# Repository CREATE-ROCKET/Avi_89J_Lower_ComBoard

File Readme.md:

> [!WARNING]
> Kicad v8を用いて作成したため、これ以下のバージョンのkicadだと動きません

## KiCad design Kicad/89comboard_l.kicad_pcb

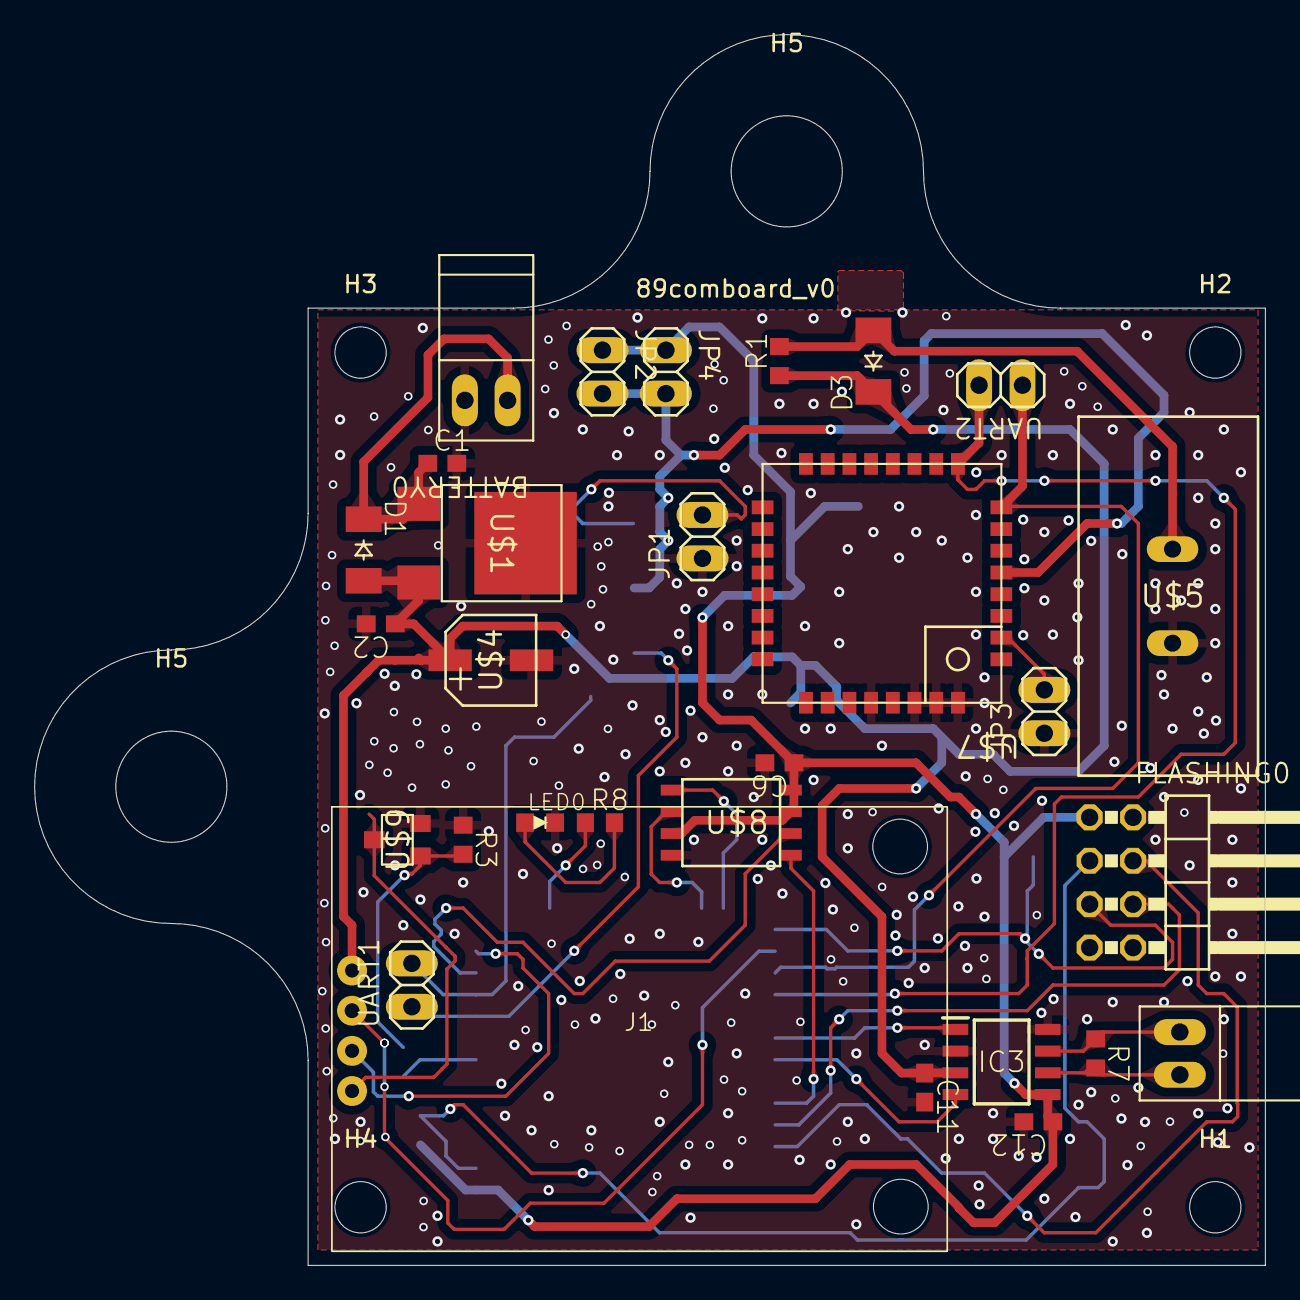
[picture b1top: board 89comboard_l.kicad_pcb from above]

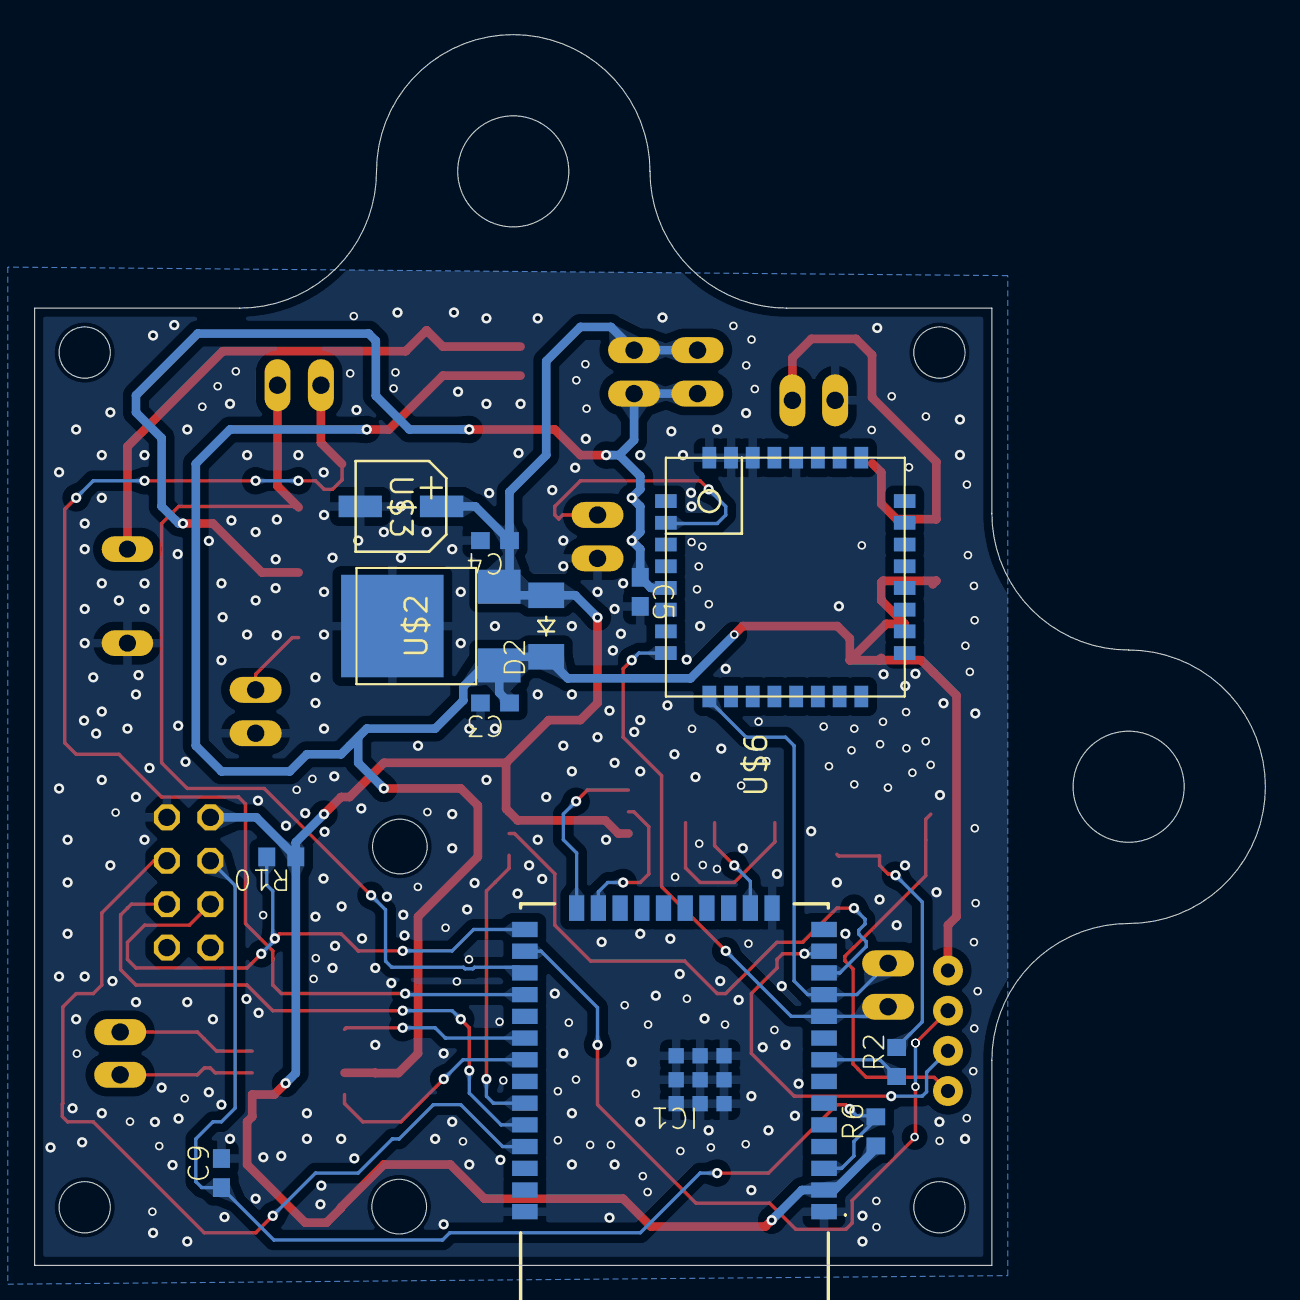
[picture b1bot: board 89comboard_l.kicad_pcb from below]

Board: 2 copper layers, 72.0 x 72.0 mm, 47 parts (12 on the bottom side), 29 nets.

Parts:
BATTERY0: L2; L_2
C1: 0.33μF; C0603_334
C2, C4: 2.2μF; C0603_334
C3: 0.33μ; C0603_334
C5, C11, C12: 0.1μ; C0603_334
C6: C-EUC0603; C0603_334
C9: 0.1u; C0603_334
CAN1: L2; L_2
D1, D2, D3: CGRM400-G; SOD-123_MINI-SMA_210
FLASHING0: PINHD-2X4/90; 2X04_90_325
H1, H2, H3, H4: MountingHole; MountingHole_3mm
H5, H5#2: MountingHole; MountingHole_6.5mm
IC1: ESP32-WROOM-32E_M113EH3200PS3Q; ESP32WROOM32EM113EH3200PS3Q0
IC3: MCP2562FD-E_SN; SOIC127P600X175-8N
J1: Conn_01x04_Socket; Neo-M8N_GPS_Module
JP1, JP2, JP3, JP4: PINHD-1X2; 1X02_325
LED0: LED1608
R1, R2: 100; R0603_334
R3, R6, R10: 10k; R0603_334
R7: 120; R0603_334
R8: 1k; R0603_334
U$1, U$2: NJM2391DL1-33
U$3, U$4: UCD0J470MCL1GS
U$5: VEC5R4355QG-I
U$6, U$7: LITE
U$8: S25FL032
U$9: SSM3K329R
UART1, UART2: PINHD-1X2; 1X02_325

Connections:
+3V3: C4.1, C6.1, C12.1, D2.A, FLASHING0.1, IC1.2 (3V3), IC3.5 (VIO), JP2.1, JP4.1, R6.1, R10.1, U$2.OUT, U$3.P$1 (+), U$8.P$3 (W#/ACC), U$8.P$7 (HOLD), U$8.P$8 (VCC)
+5V: C2.1, C3.1, C11.1, D1.A, D2.C, D3.C, IC3.3 (VDD), J1.4, R1.1, U$1.OUT, U$2.IN, U$4.P$1 (+)
/CAN_H: CAN1.1, IC3.7 (CANH), R7.1
/CAN_L: CAN1.2, IC3.6 (CANL), R7.2
/CAN_RX: IC1.31 (IO19), IC3.4 (RXD)
/CAN_TX: IC1.30 (IO18), IC3.1 (TXD)
/CON+: D3.A, R1.2, U$5.P$1 (+)
/CS: IC1.24 (IO2), U$8.P$1 (CS)
/EN: C9.1, FLASHING0.3, IC1.3 (EN), R6.2
/GPS_RXD-TX: IC1.13 (IO14), J1.2
/GPS_TXD-RX: IC1.26 (IO4), J1.3
/IO0: FLASHING0.5, IC1.25 (IO0), R10.2
/MISO: IC1.23 (IO15), U$8.P$2 (SO)
/MOSI: IC1.33 (IO21), U$8.P$5 (SI)
/ON/OFF: IC1.8 (IO32), R2.1
/RX: FLASHING0.6, IC1.34 (RXD0)
/SCK: IC1.12 (IO27), U$8.P$6 (SCK)
/TWELITE_M2S: IC1.11 (IO26), U$6.P$9 (RX), UART1.2
/TWELITE_RX: IC1.27 (IO16), U$7.P$8 (TX), UART2.1
/TWELITE_S2M: IC1.10 (IO25), U$6.P$8 (TX), UART1.1
/TWELITE_TX: IC1.28 (IO17), U$7.P$9 (RX), UART2.2
/TX: FLASHING0.4, IC1.35 (TXD0)
BAT: BATTERY0.2, C1.1, D1.C, U$1.IN
GND: BATTERY0.1, C1.2, C2.2, C3.2, C4.2, C5.2, C6.2, C9.2, C11.2, C12.2, FLASHING0.2, IC1.1 (GND_1), IC1.15 (GND_2), IC1.38 (GND_3), IC1.39 (GND_4), IC1.40 (GND_5), IC1.41 (GND_6), IC1.42 (GND_7), IC1.43 (GND_8), IC1.44 (GND_9), IC1.45 (GND_10), IC1.46 (GND_11), IC1.47 (GND_12), IC3.2 (VSS), IC3.8 (STBY), JP1.1, JP3.1, LED0.K, R3.1, U$1.GND, U$2.GND, U$3.P$2 (ー), U$4.P$2 (ー), U$5.P$2 (ー), U$6.P$28 (GND2), U$6.P$30 (GND3), U$6.P$31 (GND4), U$6.P$32 (GND5), U$7.P$28 (GND2), U$7.P$30 (GND3), U$7.P$31 (GND4), U$7.P$32 (GND5), U$8.P$4 (GND), U$9.P$2
unnamed: J1.1, U$9.P$3
unnamed: LED0.A, R8.2
unnamed: R2.2, R3.2, U$9.P$1
unnamed: JP3.2, U$7.P$2 (PRG)
VDD: C5.1, JP2.2, JP4.2, U$6.P$5 (VCC), U$7.P$5 (VCC)

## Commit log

2025-01-08 CAN senderを追加
2025-01-10 全統合の仮用
2025-01-16 ライブラリの追加
2025-01-20 gpsとflashの追加
2025-01-21 flash追加
2025-02-18 CANを新しいライブラリにした
2025-03-05 checksumの追加
2025-03-10 bansho
2025-03-10 gps.index = 0をやり忘れて、ずっと再起動し続けてた。とりあえず動いた。
2025-03-11 canを複数文字に対応
2025-03-12 時間の表示を追加。たぶん動く
2025-03-17 hoge
2025-03-17 たぶん本番
2025-03-17 pitot管の処理
2025-03-17 とりあえず動く
2025-03-17 なんか動いた
2025-03-18 シーケンス開始の合図を追加
2025-03-19 コマンドを追加
2025-03-19 色を付けた
2025-03-21 ugoku
2025-06-27 add emergency command U
2026-01-13 feat: add Kicad file
2026-01-13 feat: add sch
